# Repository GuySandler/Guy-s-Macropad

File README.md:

# Blueprint1_hackpad

The smallest macropad I could make with a screen and 8 neopixels,

# BOM:
- 1x XIAO RP2040
- 8x Cherry MX switches
- 1x 128x32 OLED Display
- 8x SK6812 MINI-E LEDs
- 8x DSA keycaps
- 4x M3x16 Bolt
- 4x M3 Heatset

# Pictures

| _Schematic_                                | _PCB_                                | _CAD_                                 | _JLC Pricing_                                | _JLC Cart_      |
| ------------------------------------------ | ------------------------------------ | ------------------------------------- | -------------------------------------        | --------------- |
|  |  |  |  | |

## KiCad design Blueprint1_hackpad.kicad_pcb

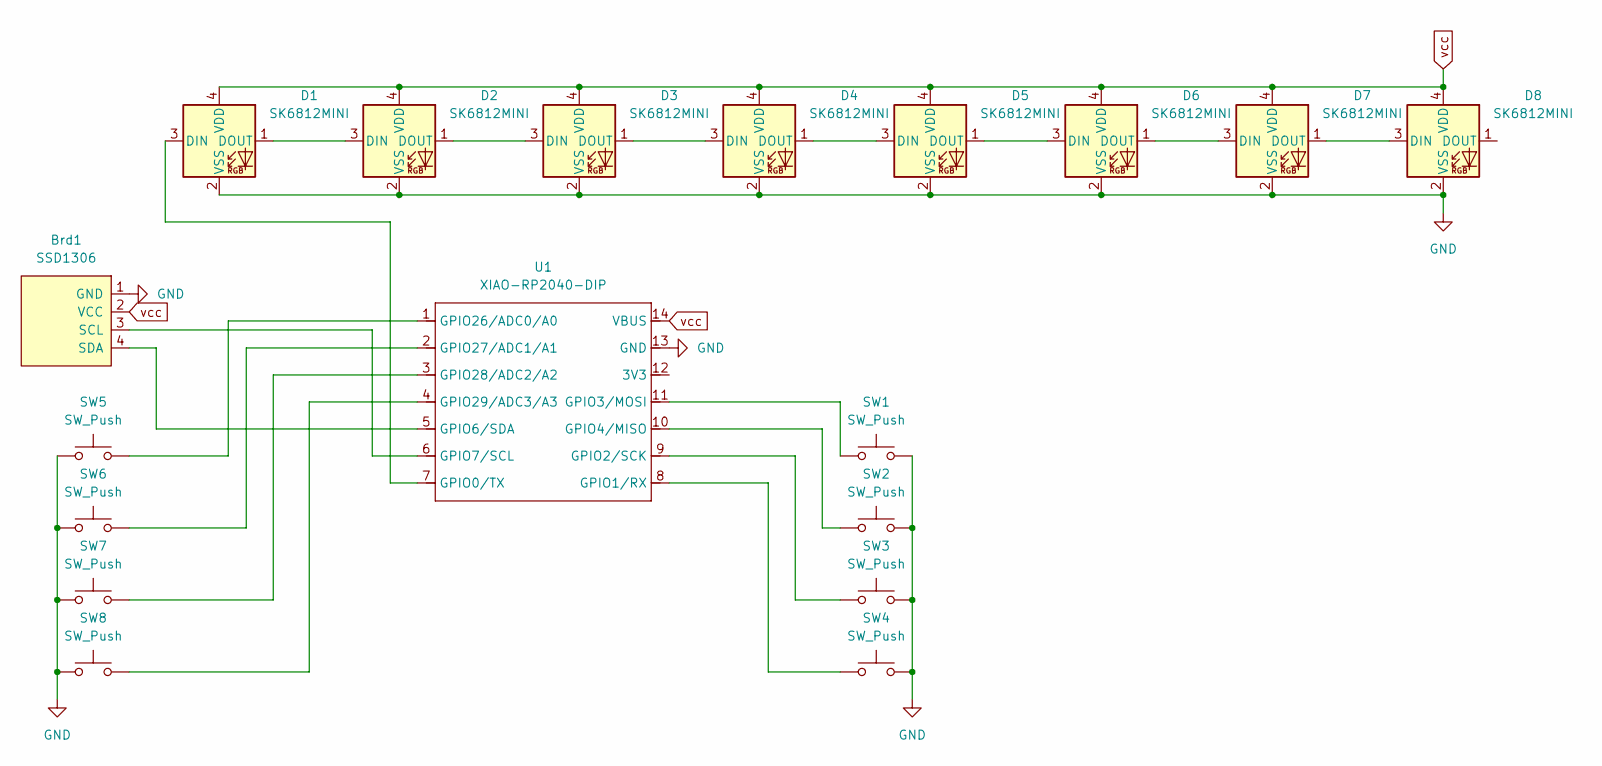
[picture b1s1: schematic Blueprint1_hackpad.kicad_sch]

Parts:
Brd1: SSD1306; SSD1306-0.91-OLED-4pin-128x32
D1, D2, D3, D4, D5, D6, D7, D8: SK6812MINI; LED_SK6812MINI_PLCC4_3.5x3.5mm_P1.75mm
SW1, SW2, SW3, SW4, SW5, SW6, SW7, SW8: SW_Push; SW_Cherry_MX_1.00u_PCB
U1: XIAO-RP2040-DIP

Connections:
GND: Brd1.1 (GND), D1.2 (VSS), D2.2 (VSS), D3.2 (VSS), D4.2 (VSS), D5.2 (VSS), D6.2 (VSS), D7.2 (VSS), D8.2 (VSS), SW1.2, SW2.2, SW3.2, SW4.2, SW5.1, SW6.1, SW7.1, SW8.1, U1.13 (GND)
unnamed: Brd1.3 (SCL), U1.6 (GPIO7/SCL)
unnamed: Brd1.4 (SDA), U1.5 (GPIO6/SDA)
unnamed: D1.3 (DIN), U1.7 (GPIO0/TX)
unnamed: D1.1 (DOUT), D2.3 (DIN)
unnamed: D2.1 (DOUT), D3.3 (DIN)
unnamed: D3.1 (DOUT), D4.3 (DIN)
unnamed: D4.1 (DOUT), D5.3 (DIN)
unnamed: D5.1 (DOUT), D6.3 (DIN)
unnamed: D6.1 (DOUT), D7.3 (DIN)
unnamed: D7.1 (DOUT), D8.3 (DIN)
unnamed: SW4.1, U1.8 (GPIO1/RX)
unnamed: SW3.1, U1.9 (GPIO2/SCK)
unnamed: SW1.1, U1.11 (GPIO3/MOSI)
unnamed: SW2.1, U1.10 (GPIO4/MISO)
unnamed: SW5.2, U1.1 (GPIO26/ADC0/A0)
unnamed: SW6.2, U1.2 (GPIO27/ADC1/A1)
unnamed: SW7.2, U1.3 (GPIO28/ADC2/A2)
unnamed: SW8.2, U1.4 (GPIO29/ADC3/A3)
vcc: Brd1.2 (VCC), D1.4 (VDD), D2.4 (VDD), D3.4 (VDD), D4.4 (VDD), D5.4 (VDD), D6.4 (VDD), D7.4 (VDD), D8.4 (VDD), U1.14 (VBUS)

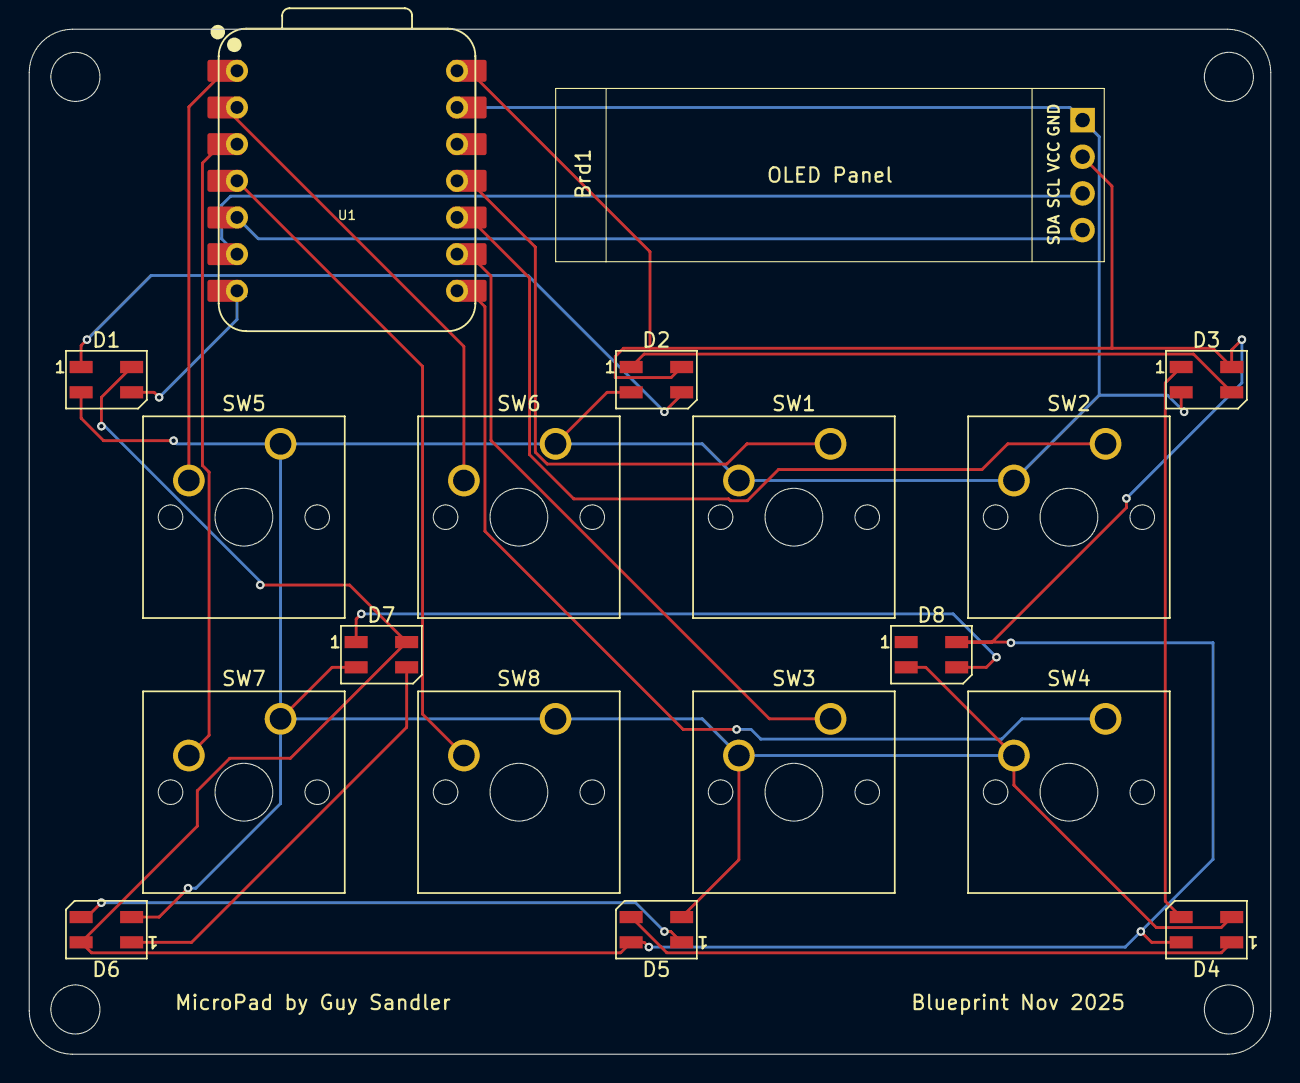
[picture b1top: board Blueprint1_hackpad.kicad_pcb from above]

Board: 2 copper layers, 86.0 x 71.0 mm, 18 parts (0 on the bottom side), 20 nets.

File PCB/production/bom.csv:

Designator,Footprint,Quantity,Value,LCSC Part #
BRD1,SSD1306-0.91-OLED-4pin-128x32,1,SSD1306,
"D1, D2, D3, D4, D5, D6, D7, D8",LED_SK6812MINI_PLCC4_3.5x3.5mm_P1.75mm,8,SK6812MINI,
"SW1, SW2, SW3, SW4, SW5, SW6, SW7, SW8",SW_Cherry_MX_1.00u_PCB,8,SW_Push,
U1,XIAO-RP2040-DIP,1,XIAO-RP2040-DIP,

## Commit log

2025-11-18 init
2025-11-18 TIME
    pcb done
2025-11-18 added screw holes
2025-11-20 added case
2025-11-20 firmware
2025-11-20 better firmware
2025-11-20 readme
2025-11-20 name fixes
2025-11-20 added pcbway proof
2025-11-20 jlc I guess
